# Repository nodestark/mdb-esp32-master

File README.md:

<div align="center">

# VMflow — MDB ESP32 Controller/Target Bridge

**A dual-port MDB bridge on the ESP32-S3, sitting between a vending machine's VMC and its peripherals.**
</div>

---

This project implements an **MDB bridge** between a vending machine's real VMC and its peripherals over the [Multi-Drop Bus](https://en.wikipedia.org/wiki/Multidrop_bus) protocol. The board exposes **two independent MDB ports**:

- **Controller port** — the board is the master: it drives the physical peripherals (coin changer `0x08` and bill validator `0x30`).
- **Target port** — the board is a slave: it emulates cashless (`0x10`), coin changer (`0x08`), and bill validator (`0x30`) toward the vending machine's real VMC.

The firmware bridges the two ports: coin/bill events detected on the controller port are relayed as MDB events on the target port (and enable/dispense/escrow commands the other way). Crucially, the target port **mirrors each physical peripheral's identity** to the VMC — its currency/country code, scale factor and decimal places — so the machine accepts them (a mismatched or unknown currency makes the VMC reject the device, e.g. `NOTE INCOMPAT`).

The cashless device (`0x10`) is **self-contained**: no physical cashless is bridged. Credit is granted out-of-band by the **VMflow payment engine** (BLE phone app) or the signed `credit` MQTT RPC, and each vend is approved locally against the session's available funds. Credit is bound to a single session — granted at Begin Session and destroyed at Session End/Reset — so no balance carries over or approves an out-of-session vend.

# Features
- **MDB controller↔target bridge**: bus poll loop, ACK/NAK/RET handling, 9-bit address/mode framing, on both an independent hardware-UART master port and a bit-banged slave port
- **Coin changer** (`0x08`) and **bill validator** (`0x30`) bridged as repeaters — the target port mirrors the real device's currency/country code, scale factor, decimal places, and tube/stacker counts, and forwards type-enable/dispense/escrow commands back to the physical device
- **Cashless** (`0x10`) **self-contained** on the target port — no physical cashless is bridged; credit is granted out-of-band and each vend is decided locally:
  - the **VMflow payment engine** — BLE (NimBLE) phone-app vend/session channel, HMAC-signed
  - the signed `credit` MQTT RPC command
  - credit is single-session (granted at Begin Session, destroyed at Session End/Reset); a vend is approved iff the item price fits the available funds
- **WiFi + MQTT** uplink (`mqtt.vmflow.xyz`) with signed remote-RPC commands (`info`, `safe`, `credit`, `oos`, `echo`, `restart`, `ota`) and telemetry (`vend_ok`, `vend_fail`, `sale`, `paxcounter`)
- **`info` RPC endpoint** reports firmware version, uptime and heap (plus a coin-vault snapshot)
- **`safe` RPC endpoint** reports cash currently in the machine: the **coin vault** (live tube count × per-coin credit — accurate) and the **bill vault** (value of bills stacked since boot; best-effort, since MDB never reports a bill's denomination once stacked), plus the raw bill stacker count
- **BLE passive-scan foot-traffic counter** ("paxcounter") — periodic scan classifying nearby phones by manufacturer ID/appearance, reported hourly
- **OTA** over HTTPS (`esp_https_ota`), triggered by the signed `ota` RPC command, pulling a release binary from this repo
- **WS2812 status LED** indicating provisioning/MQTT state
- Configurable via `idf.py menuconfig` → **VMflow** → MDB Cashless Device (currency/country code, scale factor, decimal places) — used as the fallback identity for any peripheral not (yet) online on the controller port
- Bare-metal **KiCad** hardware: MDB sockets + bridges, designed for low-cost production and customization
- Part of the open **VMflow** platform — pairs with the [📊 Web Dashboard](https://vmflow.xyz/dashboard) for telemetry, sales, inventory, and AI-powered diagnostics

# Hardware

The companion board (KiCad project [`kicad/`](kicad)) carries the ESP32-S3 module and the MDB interface bridge (TX/RX opto-isolation and the 9-bit UART path) plus the peripheral socket. Shared on PCBWay:

👉 **[MDB ESP32 Bridge Device — PCBWay](https://www.pcbway.com/project/shareproject/MDB_ESP32_Bridge_Device_ca013cf8.html)**

### MDB ports & pinout (default)

Two MDB ports — name reflects the board's role on each:

| Port            | RX  | TX  | Board role          | Connects to                                  |
|-----------------|-----|-----|---------------------|----------------------------------------------|
| **Controller**  | IO1 | IO2 | master (VMC)        | peripherals: coin changer, bill validator            |
| **Target**      | IO4 | IO5 | slave (peripheral)  | the vending machine's VMC/master             |

Both ports are driven at once by this firmware: peripherals plug into the **controller port**, the vending machine's real VMC plugs into the **target port**, and the firmware bridges the two.

Other pins:

| Signal        | GPIO    | Note                                  |
|---------------|---------|----------------------------------------|
| MDB state LED | 48      | WS2812 status LED                      |
| I2C SDA       | 10      | reserved, not used by this firmware yet |
| I2C SCL       | 11      | reserved, not used by this firmware yet |

MDB UART: 9600 baud, 9 data bits (8 data + 1 mode), even parity emulated for the 9th bit, 1 stop bit.

# Getting Started

Build with **ESP-IDF v5.x**:

```bash
# Clone the repository
git clone https://github.com/nodestark/mdb-esp32-master
cd mdb-esp32-master

idf.py menuconfig   # VMflow -> MDB Cashless Device: currency/country code, scale, decimal
idf.py build flash monitor
```

Wire the peripherals (coin changer, bill validator) to the **controller port**, and the vending machine's real VMC to the **target port**. Both sides start polling automatically — reset → setup → enable → poll. Provision WiFi/subdomain/passkey and use the cashless session from the VMflow phone app over BLE, or grant credit remotely via the signed `credit` MQTT RPC command.

# How to Contribute
- Contributions are welcome! Open issues, send pull requests, or propose new features
- Before submitting a pull request, make sure the code complies with the style and quality guidelines defined in the project
- Help improve documentation by adding usage examples, wiring notes, and peripheral compatibility reports

## License

This project is licensed under the MIT License - see the [LICENSE](LICENSE) file for details.

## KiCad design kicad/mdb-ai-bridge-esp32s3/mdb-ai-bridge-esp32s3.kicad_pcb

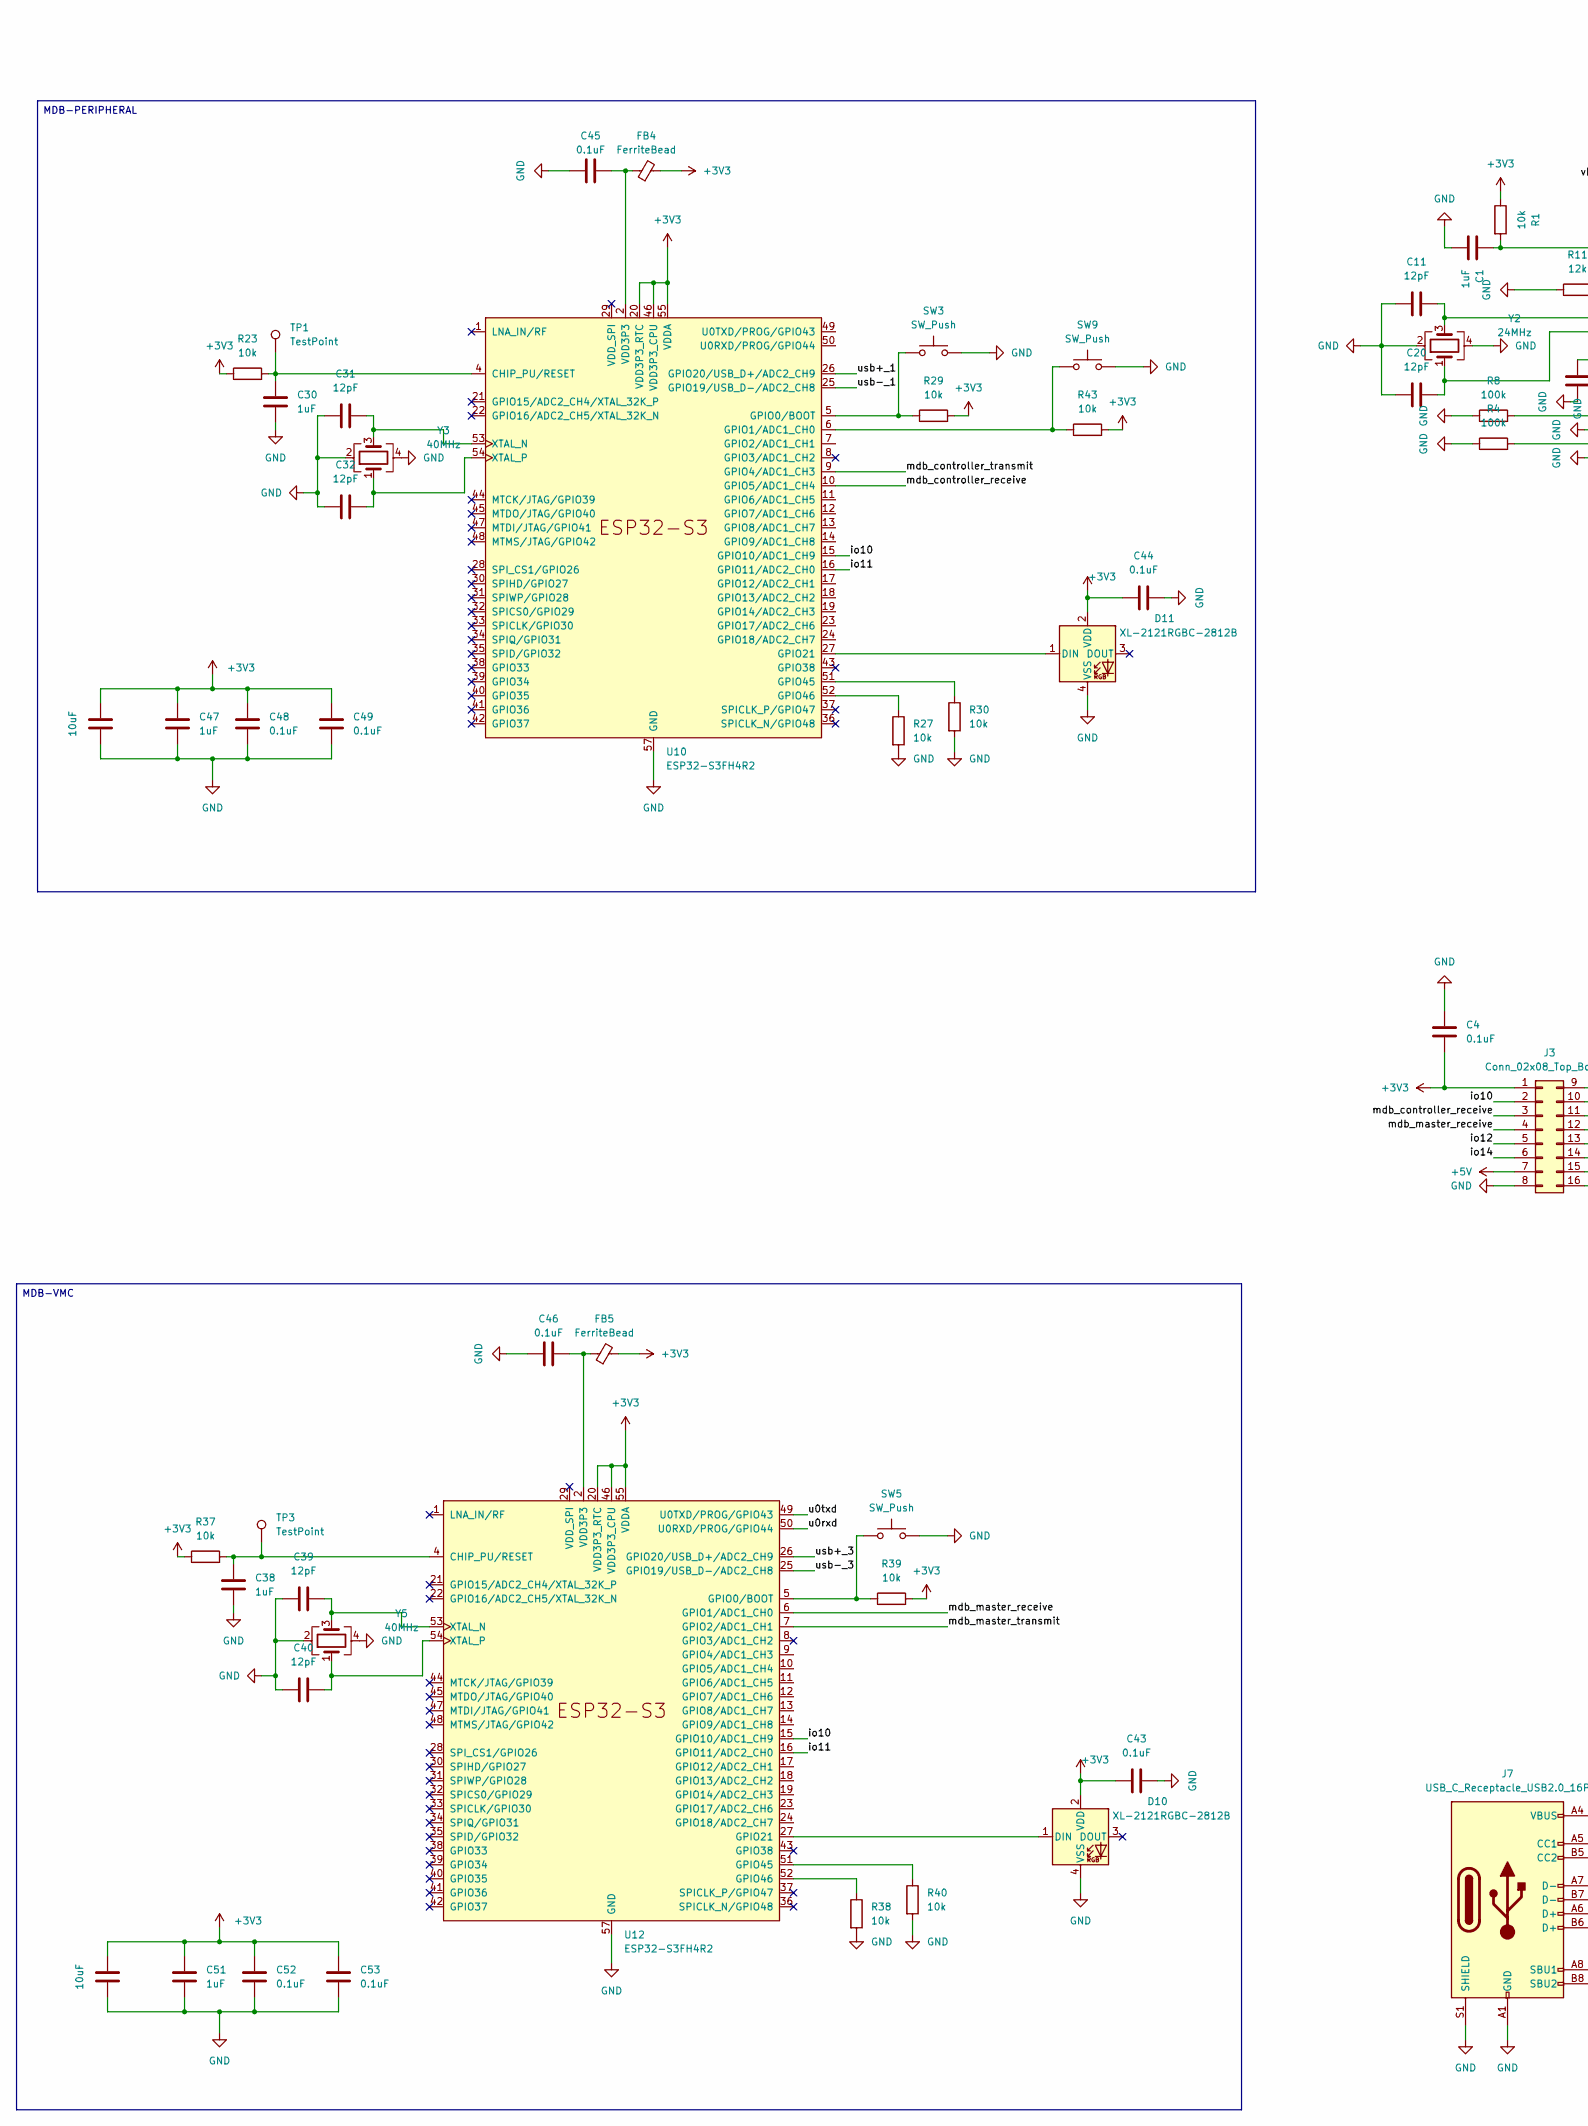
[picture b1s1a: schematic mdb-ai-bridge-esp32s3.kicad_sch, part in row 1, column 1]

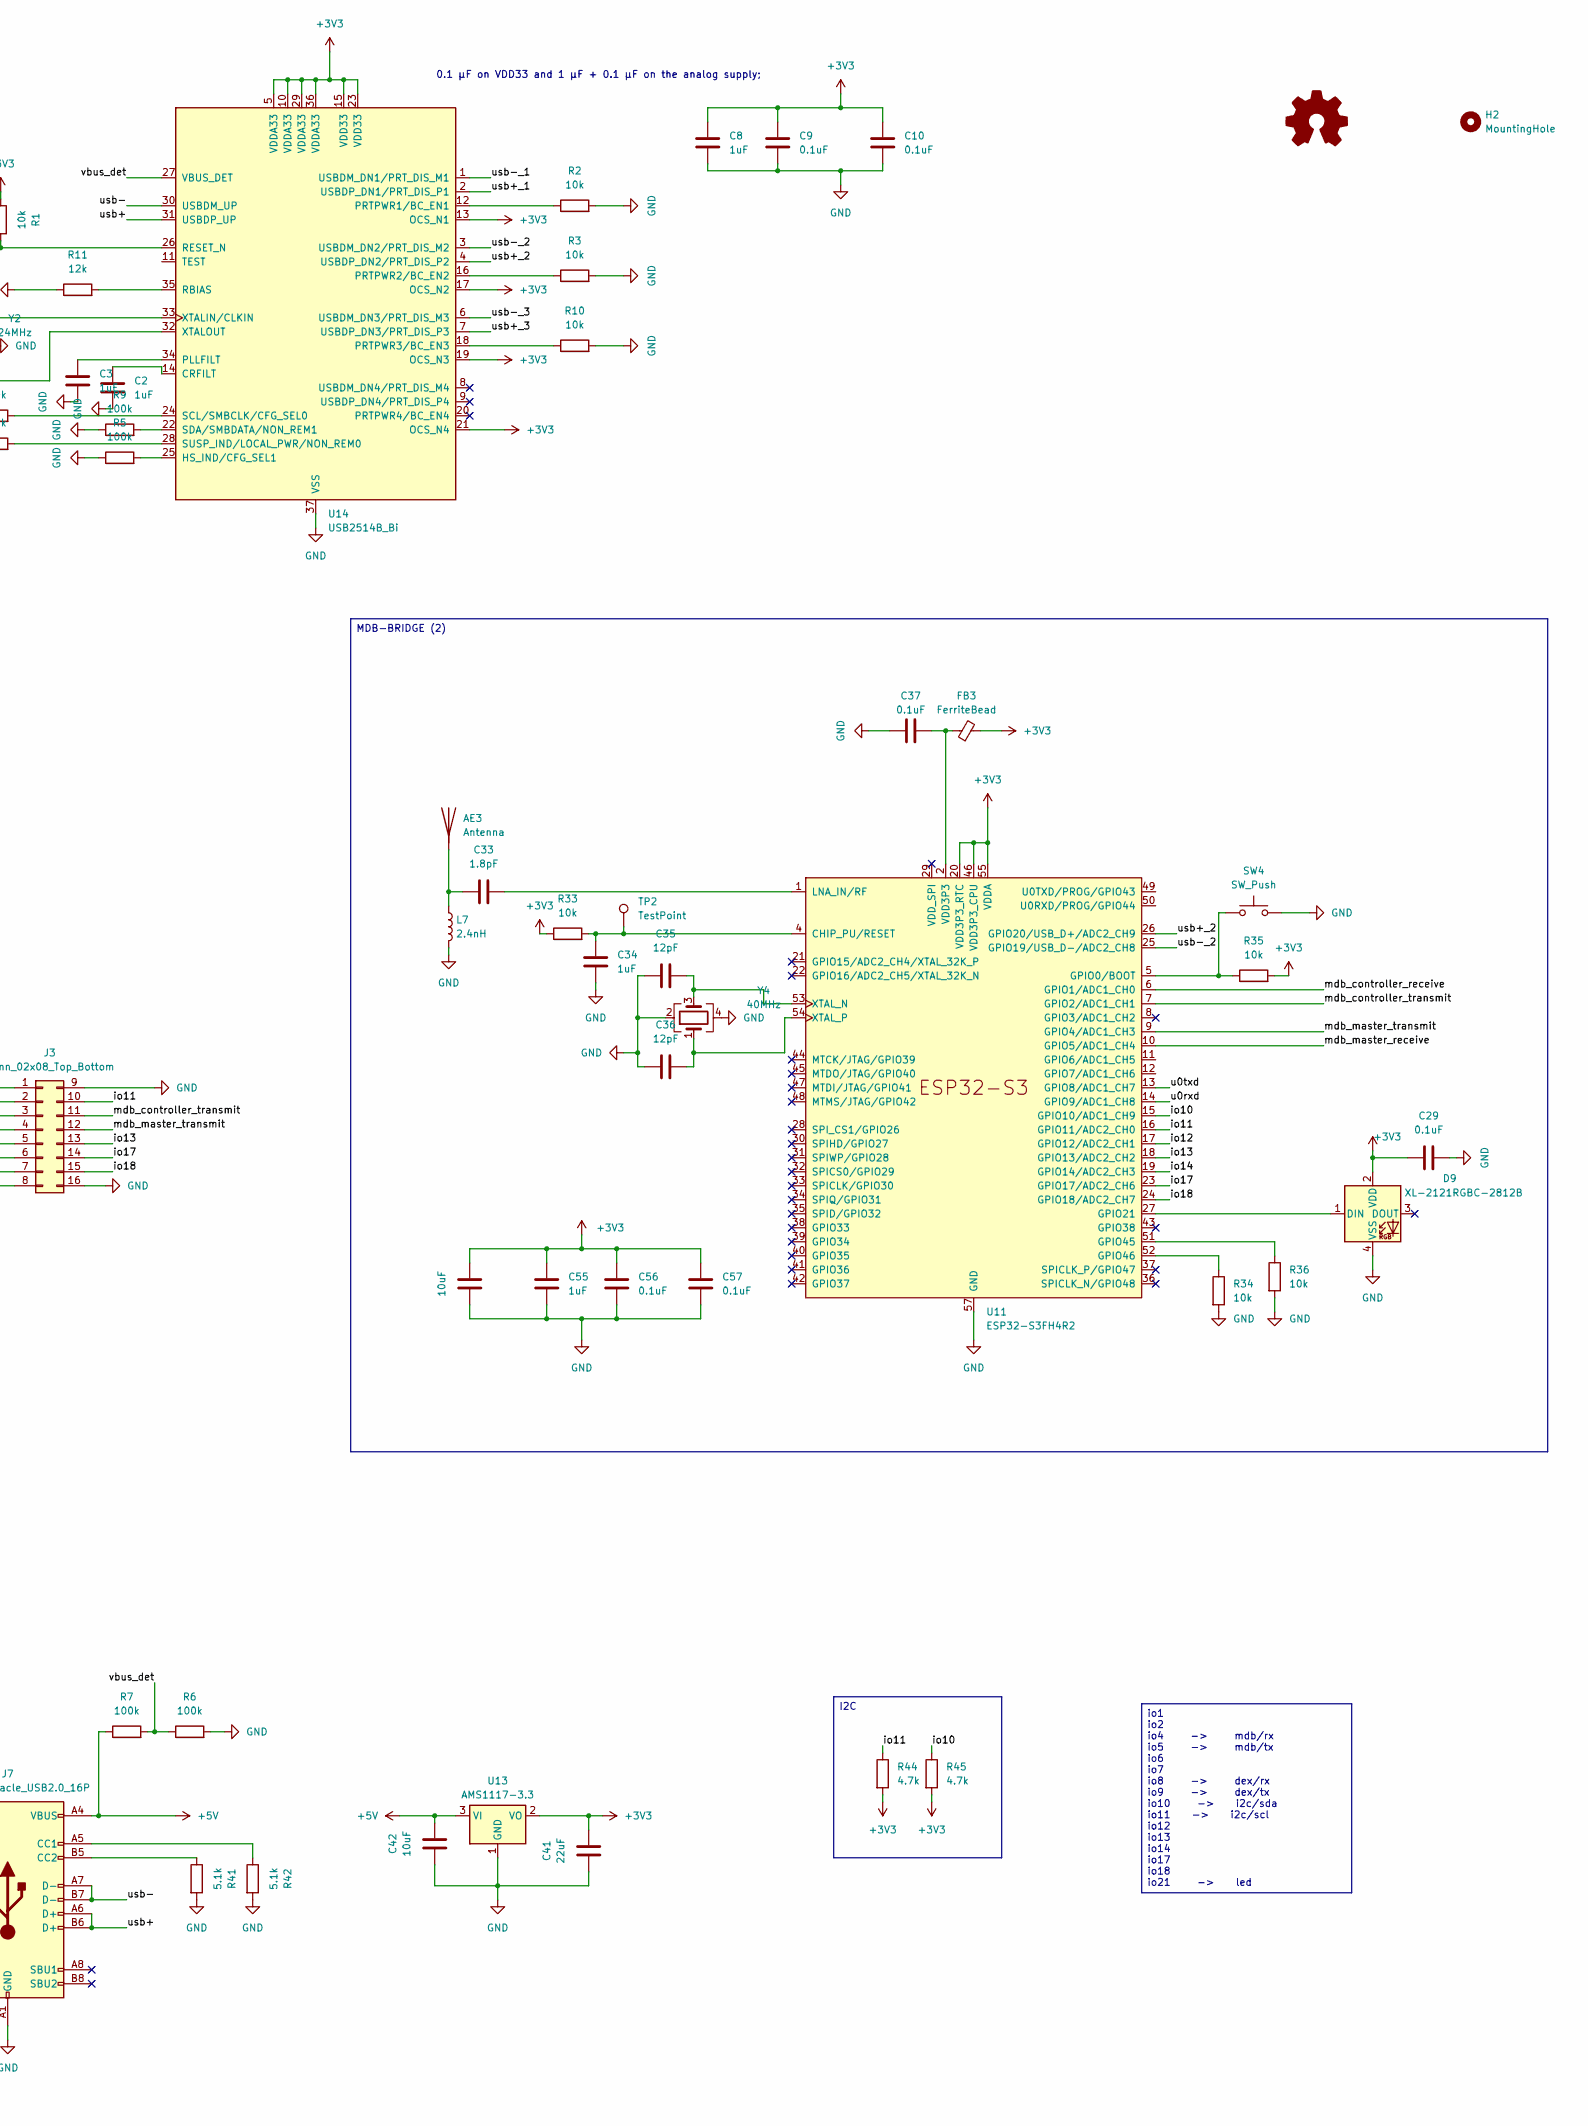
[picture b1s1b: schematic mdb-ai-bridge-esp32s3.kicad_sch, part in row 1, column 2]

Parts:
AE3: Antenna; Texas_SWRA117D_2.4GHz_Right
C1, C2, C3, C8, C30, C34, C38, C47, C51, C55: 1uF; C_0603_1608Metric; LCSC# C6119849
C4, C9, C10, C29, C37, C43, C44, C45, C46, C48, C49, C52, C53, C56, C57: 0.1uF; C_0603_1608Metric; LCSC# C5137636
C11, C20, C31, C32, C35, C36, C39, C40: 12pF; C_0603_1608Metric; LCSC# C363546
C19, C42, C50, C54: 10uF; C_0603_1608Metric; LCSC# C6119864
C33: 1.8pF; C_0603_1608Metric; LCSC# C376773
C41: 22uF; C_0603_1608Metric; LCSC# C15500
D9, D10, D11: XL-2121RGBC-2812B; LED_WS2812B-2020_PLCC4_2.0x2.0mm; LCSC# C5349957
FB3, FB4, FB5: FerriteBead; L_0603_1608Metric; LCSC# C304319
H2: MountingHole; MountingHole_2.1mm
J3: Conn_02x08_Top_Bottom; PinHeader_2x08_P2.54mm_Vertical
J7: USB_C_Receptacle_USB2.0_16P; USB_C_Receptacle_G-Switch_GT-USB-7010ASV; LCSC# C2988369
L7: 2.4nH; L_0603_1608Metric; LCSC# C2042508
R1, R2, R3, R10, R23, R27, R29, R30, R33, R34, R35, R36, R37, R38, R39, R40, R43: 10k; R_0603_1608Metric; LCSC# C98220
R4, R5, R6, R7, R8, R9: 100k; R_0603_1608Metric; LCSC# C25803
R11: 12k; R_0603_1608Metric; LCSC# C22790
R41, R42: 5.1k; R_0603_1608Metric; LCSC# C394543
R44, R45: 4.7k; R_0603_1608Metric; LCSC# C23162
SW3, SW4, SW5, SW9: SW_Push; SW_Tactile_SPST_NO_Straight_CK_PTS636Sx25SMTRLFS; LCSC# C42435421
TP1, TP2, TP3: TestPoint; TestPoint_Pad_D1.5mm
U10, U11, U12: ESP32-S3FH4R2; QFN-56-1EP_7x7mm_P0.4mm_EP4x4mm; LCSC# C3013940
U13: AMS1117-3.3; SOT-223-3_TabPin2; LCSC# C6186
U14: USB2514B_Bi; QFN-36-1EP_6x6mm_P0.5mm_EP3.7x3.7mm; LCSC# C510949
Y2: 24MHz; Crystal_SMD_3225-4Pin_3.2x2.5mm; LCSC# C19725352
Y3, Y4, Y5: 40MHz; Crystal_SMD_3225-4Pin_3.2x2.5mm; LCSC# C7294599

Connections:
+3V3: C4.1, C8.2, C9.1, C10.1, C19.2, C29.2, C41.2, C43.2, C44.2, C47.2, C48.1, C49.1, C50.2, C51.2, C52.1, C53.1, C54.2, C55.2, C56.1, C57.1, D9.2 (VDD), D10.2 (VDD), D11.2 (VDD), FB3.2, FB4.2, FB5.2, J3.1, R1.1, R23.1, R29.2, R33.1, R35.2, R37.1, R39.2, R43.2, R44.2, R45.2, U10.20 (VDD3P3_RTC), U10.46 (VDD3P3_CPU), U10.55 (VDDA), U10.56 (VDDA), U11.20 (VDD3P3_RTC), U11.46 (VDD3P3_CPU), U11.55 (VDDA), U11.56 (VDDA), U12.20 (VDD3P3_RTC), U12.46 (VDD3P3_CPU), U12.55 (VDDA), U12.56 (VDDA), U13.2 (VO), U14.5 (VDDA33), U14.10 (VDDA33), U14.13 (OCS_N1), U14.15 (VDD33), U14.17 (OCS_N2), U14.19 (OCS_N3), U14.21 (OCS_N4), U14.23 (VDD33), U14.29 (VDDA33), U14.36 (VDDA33)
+5V: C42.2, J3.7, J7.A4 (VBUS), J7.A9 (VBUS), J7.B4 (VBUS), J7.B9 (VBUS), R7.1, U13.3 (VI)
/io10: J3.2, R45.1, U10.15 (GPIO10/ADC1_CH9), U11.15 (GPIO10/ADC1_CH9), U12.15 (GPIO10/ADC1_CH9)
/io11: J3.10, R44.1, U10.16 (GPIO11/ADC2_CH0), U11.16 (GPIO11/ADC2_CH0), U12.16 (GPIO11/ADC2_CH0)
/io12: J3.5, U11.17 (GPIO12/ADC2_CH1)
/io13: J3.13, U11.18 (GPIO13/ADC2_CH2)
/io14: J3.6, U11.19 (GPIO14/ADC2_CH3)
/io17: J3.14, U11.23 (GPIO17/ADC2_CH6)
/io18: J3.15, U11.24 (GPIO18/ADC2_CH7)
/mdb_controller_receive: J3.3, U10.10 (GPIO5/ADC1_CH4), U11.6 (GPIO1/ADC1_CH0)
/mdb_controller_transmit: J3.11, U10.9 (GPIO4/ADC1_CH3), U11.7 (GPIO2/ADC1_CH1)
/mdb_master_receive: J3.4, U11.10 (GPIO5/ADC1_CH4), U12.6 (GPIO1/ADC1_CH0)
/mdb_master_transmit: J3.12, U11.9 (GPIO4/ADC1_CH3), U12.7 (GPIO2/ADC1_CH1)
/u0rxd: U11.14 (GPIO9/ADC1_CH8), U12.50 (U0RXD/PROG/GPIO44)
/u0txd: U11.13 (GPIO8/ADC1_CH7), U12.49 (U0TXD/PROG/GPIO43)
/usb+: J7.A6 (D+), J7.B6 (D+), U14.31 (USBDP_UP)
/usb+_1: U10.26 (GPIO20/USB_D+/ADC2_CH9), U14.2 (USBDP_DN1/PRT_DIS_P1)
/usb+_2: U11.26 (GPIO20/USB_D+/ADC2_CH9), U14.4 (USBDP_DN2/PRT_DIS_P2)
/usb+_3: U12.26 (GPIO20/USB_D+/ADC2_CH9), U14.7 (USBDP_DN3/PRT_DIS_P3)
/usb-: J7.A7 (D-), J7.B7 (D-), U14.30 (USBDM_UP)
/usb-_1: U10.25 (GPIO19/USB_D-/ADC2_CH8), U14.1 (USBDM_DN1/PRT_DIS_M1)
/usb-_2: U11.25 (GPIO19/USB_D-/ADC2_CH8), U14.3 (USBDM_DN2/PRT_DIS_M2)
/usb-_3: U12.25 (GPIO19/USB_D-/ADC2_CH8), U14.6 (USBDM_DN3/PRT_DIS_M3)
/vbus_det: R6.1, R7.2, U14.27 (VBUS_DET)
GND: C1.2, C2.1, C3.1, C4.2, C8.1, C9.2, C10.2, C11.1, C19.1, C20.1, C29.1, C30.2, C31.1, C32.1, C34.2, C35.1, C36.1, C37.1, C38.2, C39.1, C40.1, C41.1, C42.1, C43.1, C44.1, C45.1, C46.1, C47.1, C48.2, C49.2, C50.1, C51.1, C52.2, C53.2, C54.1, C55.1, C56.2, C57.2, D9.4 (VSS), D10.4 (VSS), D11.4 (VSS), J3.8, J3.9, J3.16, J7.A1 (GND), J7.A12 (GND), J7.B1 (GND), J7.B12 (GND), J7.S1 (SHIELD), L7.2, R2.2, R3.2, R4.1, R5.1, R6.2, R8.1, R9.1, R10.2, R11.1, R27.2, R30.2, R34.2, R36.2, R38.2, R40.2, R41.2, R42.2, SW3.2, SW4.2, SW5.2, SW9.2, U10.57 (GND), U11.57 (GND), U12.57 (GND), U13.1 (GND), U14.37 (VSS), Y2.2, Y2.4, Y3.2, Y3.4, Y4.2, Y4.4, Y5.2, Y5.4
unnamed: AE3.1 (A), C33.1, L7.1
unnamed: D9.1 (DIN), U11.27 (GPIO21)
unnamed: D10.1 (DIN), U12.27 (GPIO21)
unnamed: D11.1 (DIN), U10.27 (GPIO21)
unnamed: J7.A5 (CC1), R42.1
unnamed: J7.B5 (CC2), R41.1
unnamed: C30.1, R23.2, TP1.1, U10.4 (CHIP_PU/RESET)
unnamed: R29.1, SW3.1, U10.5 (GPIO0/BOOT)
unnamed: R43.1, SW9.1, U10.6 (GPIO1/ADC1_CH0)
unnamed: R30.1, U10.51 (GPIO45)
unnamed: R27.1, U10.52 (GPIO46)
unnamed: C31.2, U10.53 (XTAL_N), Y3.3
unnamed: C32.2, U10.54 (XTAL_P), Y3.1
unnamed: C34.1, R33.2, TP2.1, U11.4 (CHIP_PU/RESET)
unnamed: R35.1, SW4.1, U11.5 (GPIO0/BOOT)
unnamed: R36.1, U11.51 (GPIO45)
unnamed: R34.1, U11.52 (GPIO46)
unnamed: C33.2, U11.1 (LNA_IN/RF)
unnamed: C35.2, U11.53 (XTAL_N), Y4.3
unnamed: C36.2, U11.54 (XTAL_P), Y4.1
unnamed: C38.1, R37.2, TP3.1, U12.4 (CHIP_PU/RESET)
unnamed: R39.1, SW5.1, U12.5 (GPIO0/BOOT)
unnamed: R40.1, U12.51 (GPIO45)
unnamed: R38.1, U12.52 (GPIO46)
unnamed: C39.2, U12.53 (XTAL_N), Y5.3
unnamed: C40.2, U12.54 (XTAL_P), Y5.1
unnamed: C2.2, U14.14 (CRFILT)
unnamed: R5.2, U14.25 (HS_IND/CFG_SEL1)
unnamed: C3.2, U14.34 (PLLFILT)
unnamed: R2.1, U14.12 (PRTPWR1/BC_EN1)
unnamed: R3.1, U14.16 (PRTPWR2/BC_EN2)
unnamed: R10.1, U14.18 (PRTPWR3/BC_EN3)
unnamed: R11.2, U14.35 (RBIAS)
unnamed: C1.1, R1.2, U14.26 (RESET_N)
unnamed: R8.2, U14.24 (SCL/SMBCLK/CFG_SEL0)
unnamed: R9.2, U14.22 (SDA/SMBDATA/NON_REM1)
unnamed: R4.2, U14.28 (SUSP_IND/LOCAL_PWR/NON_REM0)
unnamed: C11.2, U14.33 (XTALIN/CLKIN), Y2.3
unnamed: C20.2, U14.32 (XTALOUT), Y2.1

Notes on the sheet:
0.1 µF on VDD33 and 1 µF + 0.1 µF on the analog supply;
MDB-PERIPHERAL
MDB-BRIDGE (2)
MDB-VMC
io1 io2 io4 -> mdb/rx io5 -> mdb/tx io6 io7 io8 -> dex/rx io9 -> dex/tx io10 -> i2c/sda io11 -> i2c/scl io12 io13 io14 io17 io18 io21 -> led
I2C

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
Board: 2 copper layers, 94 parts (0 on the bottom side), 65 nets, no tracks yet.

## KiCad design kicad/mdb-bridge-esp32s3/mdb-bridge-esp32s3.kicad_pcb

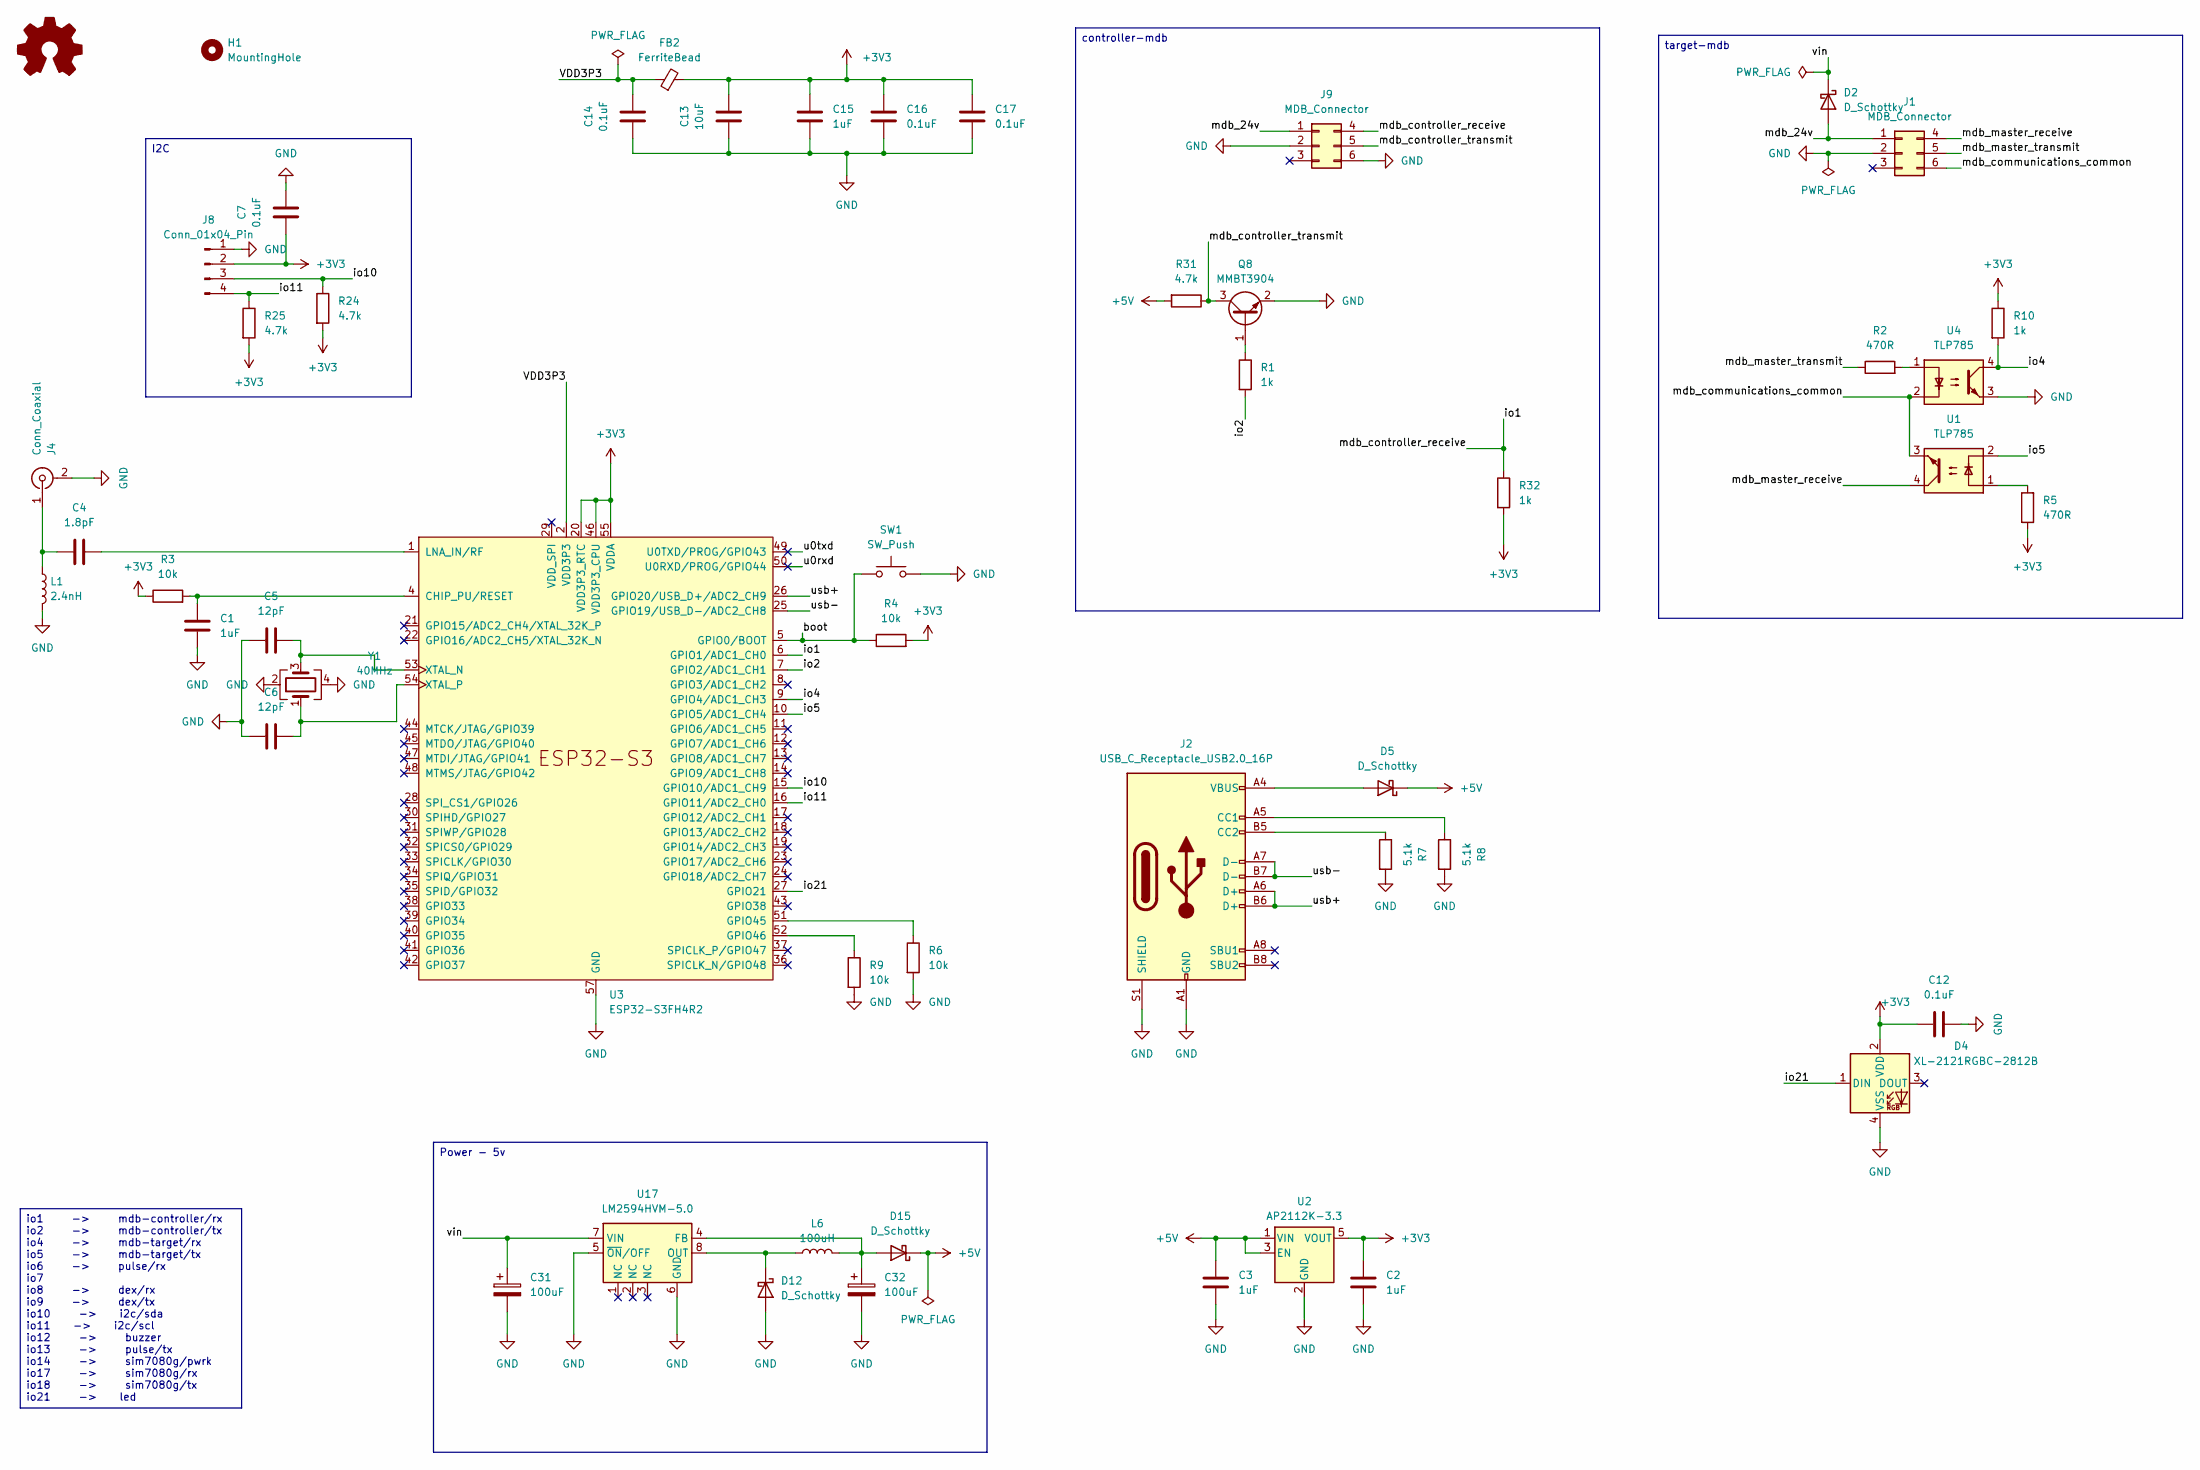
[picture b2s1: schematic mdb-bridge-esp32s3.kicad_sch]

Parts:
C1, C2, C3, C15: 1uF; C_0603_1608Metric; LCSC# C696901
C4: 1.8pF; C_0603_1608Metric; LCSC# C376773
C5, C6: 12pF; C_0603_1608Metric; LCSC# C363546
C7, C12, C14, C16, C17: 0.1uF; C_0603_1608Metric; LCSC# C5137636
C13: 10uF; C_0603_1608Metric; LCSC# C6119864
C31: 100uF; CP_Elec_6.3x5.8; LCSC# C128464
C32: 100uF; CP_EIA-3528-21_Kemet-B; LCSC# C90975
D2, D5, D12, D15: D_Schottky; D_SOD-123; LCSC# C18195164
D4: XL-2121RGBC-2812B; LED_WS2812B-2020_PLCC4_2.0x2.0mm; LCSC# C5349957
FB2: FerriteBead; L_0603_1608Metric; LCSC# C304319
H1: MountingHole; MountingHole_2.1mm
J1, J9: MDB_Connector; Molex_Mini-Fit_Jr_5566-06A_2x03_P4.20mm_Vertical; LCSC# C22365701
J2: USB_C_Receptacle_USB2.0_16P; USB_C_Receptacle_G-Switch_GT-USB-7010ASV; LCSC# C2988369
J4: Conn_Coaxial; U.FL_Hirose_U.FL-R-SMT-1_Vertical; LCSC# C88374
J8: Conn_01x04_Pin; JST_PH_B4B-PH-K_1x04_P2.00mm_Vertical; LCSC# C131334
L1: 2.4nH; L_0603_1608Metric; LCSC# C2042508
L6: 100uH; L_7.3x7.3_H3.5; LCSC# C182195
Q8: MMBT3904; SOT-23; LCSC# C916374
R1, R10, R32: 1k; R_0603_1608Metric; LCSC# C2907113
R2, R5: 470R; R_0603_1608Metric; LCSC# C114669
R3, R4, R6, R9: 10k; R_0603_1608Metric; LCSC# C98220
R7, R8: 5.1k; R_0603_1608Metric; LCSC# C394543
R24, R25, R31: 4.7k; R_0603_1608Metric; LCSC# C23162
SW1: SW_Push; SW_Tactile_SPST_NO_Straight_CK_PTS636Sx25SMTRLFS; LCSC# C42435421
U1, U4: TLP785; SOP-4_3.8x4.1mm_P2.54mm; LCSC# C45445
U2: AP2112K-3.3; SOT-23-5; LCSC# C51118
U3: ESP32-S3FH4R2; QFN-56-1EP_7x7mm_P0.4mm_EP4x4mm; LCSC# C3013940
U17: LM2594HVM-5.0; SOIC-8_3.9x4.9mm_P1.27mm; LCSC# C2904794
Y1: 40MHz; Crystal_SMD_3225-4Pin_3.2x2.5mm; LCSC# C7294599

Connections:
+3V3: C2.2, C7.1, C12.2, C13.2, C15.2, C16.1, C17.1, D4.2 (VDD), FB2.2, J8.2, R3.1, R4.2, R5.1, R10.1, R24.2, R25.2, R32.2, U2.5 (VOUT), U3.20 (VDD3P3_RTC), U3.46 (VDD3P3_CPU), U3.55 (VDDA), U3.56 (VDDA)
+5V: C3.2, D5.1 (K), D15.1 (K), R31.2, U2.1 (VIN), U2.3 (EN)
/boot: R4.1, SW1.1, U3.5 (GPIO0/BOOT)
/io1: J9.4, R32.1, U3.6 (GPIO1/ADC1_CH0)
/io2: R1.2, U3.7 (GPIO2/ADC1_CH1)
/io4: R10.2, U3.9 (GPIO4/ADC1_CH3), U4.4
/io5: U1.2, U3.10 (GPIO5/ADC1_CH4)
/io10: J8.3, R24.1, U3.15 (GPIO10/ADC1_CH9)
/io11: J8.4, R25.1, U3.16 (GPIO11/ADC2_CH0)
/io21: D4.1 (DIN), U3.27 (GPIO21)
/mdb_24v: D2.2 (A), J1.1, J9.1
/mdb_communications_common: J1.6, U1.3, U4.2
/mdb_controller_transmit: J9.5, Q8.3 (C), R31.1
/mdb_master_receive: J1.4, U1.4
/mdb_master_transmit: J1.5, R2.1
/u0rxd: U3.50 (U0RXD/PROG/GPIO44)
/u0txd: U3.49 (U0TXD/PROG/GPIO43)
/usb+: J2.A6 (D+), J2.B6 (D+), U3.26 (GPIO20/USB_D+/ADC2_CH9)
/usb-: J2.A7 (D-), J2.B7 (D-), U3.25 (GPIO19/USB_D-/ADC2_CH8)
/vin: C31.1, D2.1 (K), U17.7 (VIN)
GND: C1.2, C2.1, C3.1, C5.1, C6.1, C7.2, C12.1, C13.1, C14.1, C15.1, C16.2, C17.2, C31.2, C32.2, D4.4 (VSS), D12.2 (A), J1.2, J2.A1 (GND), J2.A12 (GND), J2.B1 (GND), J2.B12 (GND), J2.S1 (SHIELD), J4.2 (Ext), J8.1, J9.2, J9.6, L1.2, Q8.2 (E), R6.2, R7.2, R8.2, R9.2, SW1.2, U2.2 (GND), U3.57 (GND), U4.3, U17.5 (~ON/OFF), U17.6 (GND), Y1.2, Y1.4
unnamed: D5.2 (A), J2.A4 (VBUS), J2.A9 (VBUS), J2.B4 (VBUS), J2.B9 (VBUS)
unnamed: D12.1 (K), L6.1, U17.8 (OUT)
unnamed: C32.1, D15.2 (A), L6.2, U17.4 (FB)
unnamed: J2.A5 (CC1), R8.1
unnamed: J2.B5 (CC2), R7.1
unnamed: C4.1, J4.1 (In), L1.1
unnamed: Q8.1 (B), R1.1
unnamed: R2.2, U4.1
unnamed: R5.2, U1.1
unnamed: C1.1, R3.2, U3.4 (CHIP_PU/RESET)
unnamed: R6.1, U3.51 (GPIO45)
unnamed: R9.1, U3.52 (GPIO46)
unnamed: C4.2, U3.1 (LNA_IN/RF)
unnamed: C5.2, U3.53 (XTAL_N), Y1.3
unnamed: C6.2, U3.54 (XTAL_P), Y1.1
VDD3P3: C14.2, FB2.1, U3.2 (VDD3P3), U3.3 (VDD3P3)

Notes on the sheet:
io1 -> mdb-controller/rx io2 -> mdb-controller/tx io4 -> mdb-target/rx io5 -> mdb-target/tx io6 -> pulse/rx io7 io8 -> dex/rx io9 -> dex/tx io10 -> i2c/sda io11 -> i2c/scl io12 -> buzzer io13 -> pulse/tx io14 -> sim7080g/pwrk io17 -> sim7080g/rx io18 -> sim7080g/tx io21 -> led
controller-mdb
Power - 5v
I2C
target-mdb

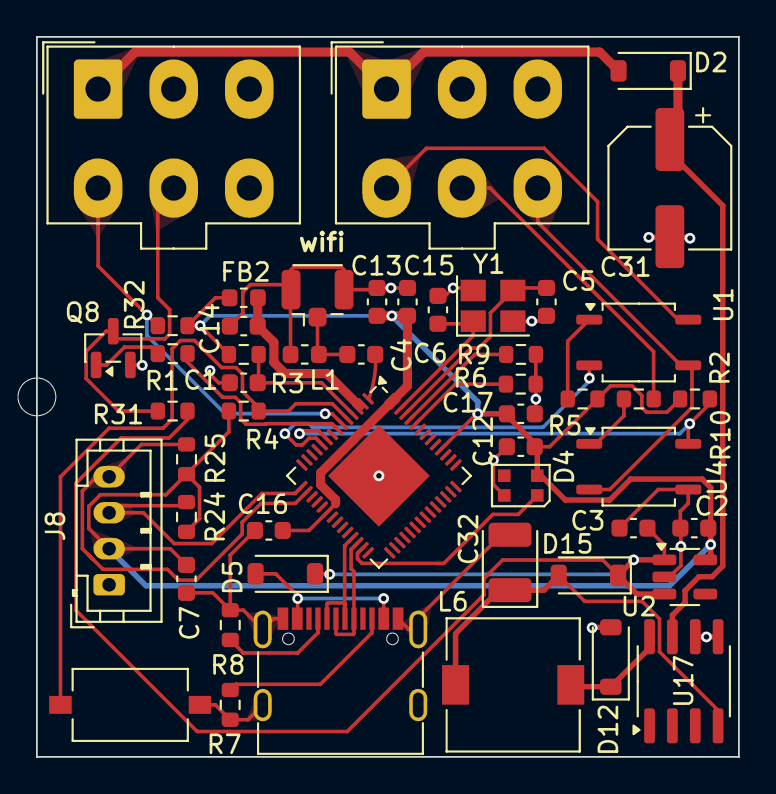
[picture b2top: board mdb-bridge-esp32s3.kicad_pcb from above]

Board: 2 copper layers, 39.0 x 40.0 mm, 51 parts (0 on the bottom side), 35 nets.

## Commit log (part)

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2026-06-03 Remove VMflow Ecosystem section from README
    Removed the VMflow Ecosystem section from the README.
2026-06-07 fix(mdb): widen POLL window to 60ms and poll-fail threshold to 10
    Bench-validated against the mdb-bill-reader emulator on a live MDB bus:
    - ENABLED-state POLL read for changer (0x08) and validator (0x30) used a 30ms
    window. A real peripheral can spread its multi-byte deposit/bill event reply
    past 30ms, truncating the read so the coin/bill event was lost. Widen to 60ms
    (costs ~30ms more per idle poll, which already blocks the full window).
    - poll_fail_count threshold of 3 dropped a device to INACTIVE on a brief bus
2026-06-15 tlp7185^Co tlp785
2026-06-19 Add MDB PCB connection diagram to README
    Added a diagram of the MDB PCB connection to the README.
2026-06-19 Remove duplicate MDB PCB connection diagram
    Removed duplicate MDB PCB connection diagram from README.

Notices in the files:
README.md:
License: MIT
